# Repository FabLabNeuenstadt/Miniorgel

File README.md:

# Miniorgel / mini organ

# The mini organ is a astable multivibrator with 8 potentiometers and 8 push buttons and a loudspeaker. this will be used as soldering project in our fablab.

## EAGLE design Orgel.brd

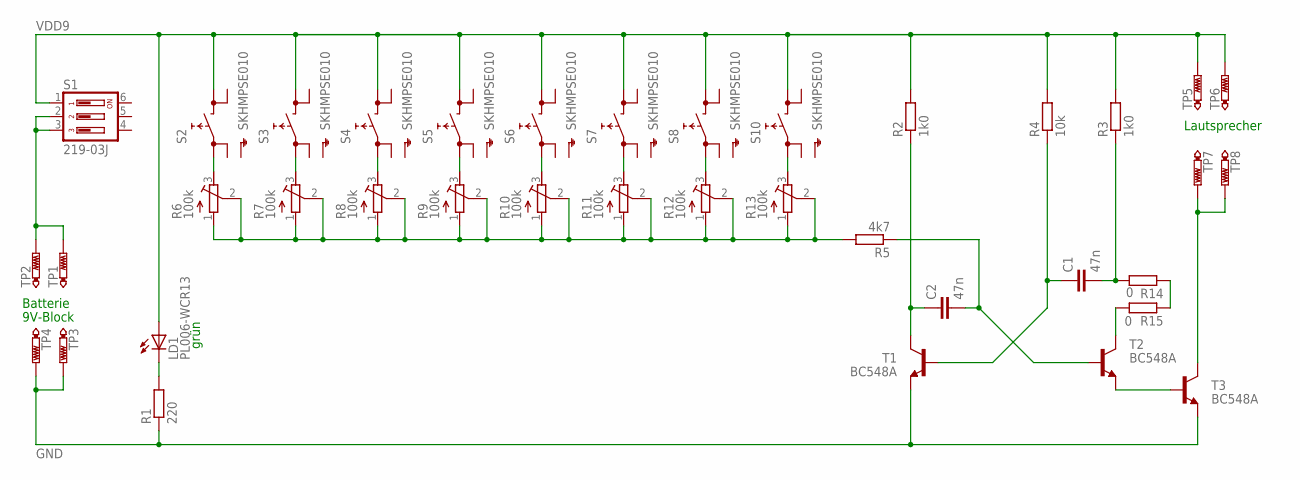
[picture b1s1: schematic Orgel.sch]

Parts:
C1, C2: 47n; C1206
LD1: PL006-WCR13; SOT23
R1: 220; M1206
R2, R3: 1k0; M1206
R4: 10k; M1206
R5: 4k7; M1206
R6, R7, R8, R9, R10, R11, R12, R13: 100k; RTRIM5X
R14, R15: 0; M5923
S1: 219-03J; CTS-219-03J
S2, S3, S4, S5, S6, S7, S8, S10: SKHMPSE010; SKHMPXE010
T1, T2, T3: BC548A; SOT23-EBC
TP1, TP2, TP3, TP4, TP5, TP6, TP7, TP8: PTR1TP20SQ; TP20SQ

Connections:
GND: R1.1, T1.E, T3.E, TP3.TP, TP4.TP
unnamed: R6.3 (E), S2.1 (1.1)
unnamed: C2.1, R2.1, T1.C
unnamed: LD1.3 (C), R1.2
unnamed: R5.2, R6.1 (A), R6.2 (S), R7.1 (A), R7.2 (S), R8.1 (A), R8.2 (S), R9.1 (A), R9.2 (S), R10.1 (A), R10.2 (S), R11.1 (A), R11.2 (S), R12.1 (A), R12.2 (S), R13.1 (A), R13.2 (S)
unnamed: T2.E, T3.B
unnamed: C2.2, R5.1, T2.B
unnamed: S1.2, S1.3, TP1.TP, TP2.TP
unnamed: C1.2, R3.1, R14.2
unnamed: R14.1, R15.1
unnamed: R7.3 (E), S3.1 (1.1)
unnamed: R8.3 (E), S4.1 (1.1)
unnamed: R15.2, T2.C
unnamed: C1.1, R4.1, T1.B
unnamed: R11.3 (E), S7.1 (1.1)
unnamed: R10.3 (E), S6.1 (1.1)
unnamed: R9.3 (E), S5.1 (1.1)
unnamed: T3.C, TP7.TP, TP8.TP
unnamed: R13.3 (E), S10.1 (1.1)
unnamed: R12.3 (E), S8.1 (1.1)
VDD9: LD1.1 (A), R2.2, R3.2, R4.2, S1.1, S2.3 (2.1), S3.3 (2.1), S4.3 (2.1), S5.3 (2.1), S6.3 (2.1), S7.3 (2.1), S8.3 (2.1), S10.3 (2.1), TP5.TP, TP6.TP

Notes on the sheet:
Batterie
9V-Block
Lautsprecher
grün

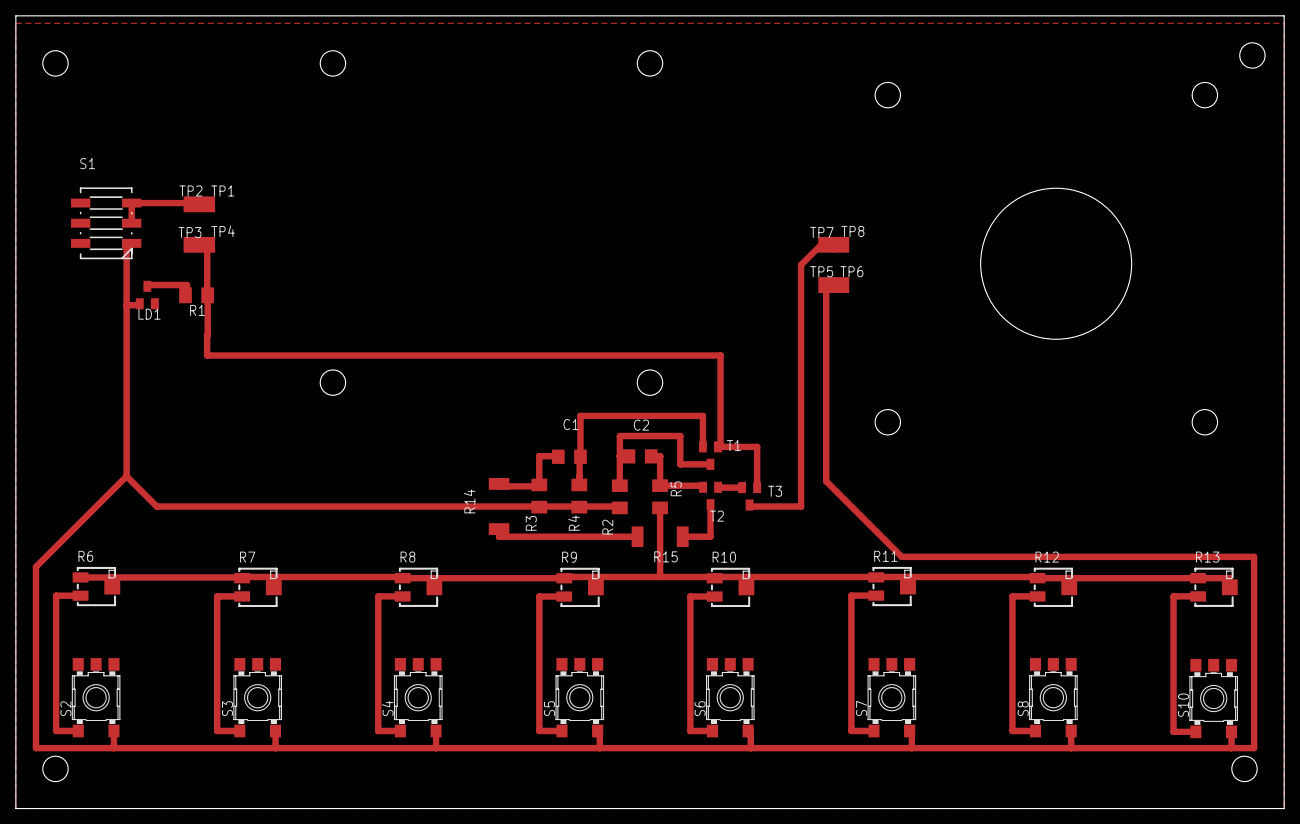
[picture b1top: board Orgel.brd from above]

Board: 2 copper layers, 160.0 x 100.0 mm, 38 parts (0 on the bottom side), 21 nets.

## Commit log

2016-03-01 Added files via upload
